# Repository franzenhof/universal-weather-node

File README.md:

# Universal Weather Node — Wireless Sensor Receiver, Weather Station and Gateway for Bresser, Ecowitt / Froggit, TFA and Davis Sensors

**Turn a €20 ESP32 board into the hub of your weather station.** A **Heltec WiFi LoRa 32 V4** (or V3) receives your wireless outdoor station **directly on 868 MHz** — no console, no vendor gateway, no Raspberry Pi, no cloud — measures with its own sensors where you add them, computes dew point, trends and rain totals, and passes everything on to **Home Assistant (MQTT)**, **Loxone**, its own **web dashboard**, **weather networks** and, optionally, **LoRaWAN**.

<!-- help:skip -->

<!-- /help:skip -->

## What to Buy

For a wireless station — no soldering, no custom PCB:

| Part | Notes | Approx. price |
|------|-------|---------------|
| **Heltec WiFi LoRa 32 V4** *(strongly recommended — firmware 4.x)* or **V3 / V3.1 / V3.2** *(legacy)* | The **868 MHz** version (EU). The **V4** has an RF front end with a low-noise amplifier (helps with weak or distant sensors) and 2 MB PSRAM (ESP32-S3R2; used for the history, large buffers and HTTPS since 2.0.0-rc.9) plus 16 MB flash; the firmware detects it and switches the front end itself. **The V4 is strongly recommended:** this 3.x line is legacy (bug fixes only); all new functions come with firmware 4.x, which runs on the V4 only. On a V3, 3.x keeps working. For wired sensors (Davis cups and vane, reed switches, DS18B20 …) use the [custom PCB v2.0](docs/pcb.md#custom-pcb): it takes a **V3 or a V4** (one socket set each, see [Heltec V3 or V4 on the PCB](docs/pcb.md#heltec-v3-or-v4-on-the-pcb)); the older Rev 1.2 / 1.3 boards take the V3 only. Not supported: **V4-R8** (ESP32-S3R8): its 8 MB octal PSRAM takes GPIO33–37, which the board and the PCB need — buy the standard V4 with the **ESP32-S3R2**. | €20–30 |
| **868 MHz antenna** | The small antenna that comes with the board is fine for sensors nearby. For more range, an external 868 MHz antenna with a u.FL/IPEX-to-SMA pigtail (the [enclosure](docs/minimal-build.md) has an SMA bulkhead). **Never power the board without an antenna.** | €0–15 |
| **USB-C power supply** 5 V, ≥ 1 A, with cable | any phone charger | €5–10 |
| **BME280 module** (I²C, 3.3 V) — *recommended* | Adds the air pressure (pressure trend, weather networks); four jumper wires, see [Minimal Wireless Build](docs/minimal-build.md). Must be a BME280, not a BMP280. Not needed if an Ecowitt WS69 pressure module or a WN32P already sends pressure. | €5–10 |
| **Enclosure** — optional | 3D-printable case with a separate ventilated BME280 chamber in [`3dprint/`](3dprint/README.md) (designed for the V3 — check the fit for a V4), or any small box in a dry, sheltered place | – |
| **Your wireless sensors** | 868 MHz versions of Bresser 5/6/7-in-1 and other Bresser sensors, Ecowitt / Froggit, TFA / LaCrosse IT+; Davis Vantage Pro2 / Vue EU (experimental) | – |

Prices are rough guides and vary by shop. For the installation you need a computer with **Chrome or Edge** once.

## Quick Start (wireless station, about 15 minutes)

**You need:** the parts from [What to Buy](#what-to-buy) — a **Heltec WiFi LoRa 32 V4 or V3** (see [installation](docs/installation.md#installing-the-firmware-browser-no-software)) with its **868 MHz antenna**, a USB-C power supply, and a wireless outdoor station — **Bresser** 5/6/7-in-1, **Ecowitt / Froggit** (WS69, WS80, WS85, WS90, WH31, WN34, WH51, WH57, air quality, leak …) or **TFA / LaCrosse IT+**. Recommended: a **BME280** module for the air pressure (four jumper wires, see [Minimal Wireless Build](docs/minimal-build.md)).

1. **Install the firmware in the browser** — Chrome/Edge, [web.esphome.io](https://web.esphome.io), the `-factory.bin` from [`firmware/`](firmware/). Step by step: [Installing the Firmware](docs/installation.md#installing-the-firmware-browser-no-software).
2. **Connect your phone** to the Wi-Fi **`WeatherNode`** and open **http://192.168.4.1** (opens by itself on most phones).
3. **Choose your Wi-Fi** (*Configure WiFi*), save. The node restarts and joins your network.
4. **Open the IP address shown on the display** (in your own network). The **setup wizard** starts by itself and takes you through language, your wireless station (it searches by itself for Bresser, Ecowitt / Froggit and TFA — mark yours with ★, hide the neighbours'), location and altitude, units, an admin password, and optionally [MQTT for Home Assistant](docs/mqtt-home-assistant.md), [weather networks](docs/weather-networks.md) and Loxone. Every step can be skipped — see [Setup Wizard](docs/installation.md#setup-wizard).
5. **Done.** The dashboard shows live values after one measurement cycle; everything can be changed later under **Settings**.

Wired sensors (Davis, reed switches, DS18B20 …) need one of the [custom PCBs](docs/pcb.md#custom-pcb) — see [Hardware](docs/pcb.md#hardware). [LoRaWAN](docs/lorawan.md) is off by default; switch it on for sites without Wi-Fi.

## Features

- 📻 **Up to 32 wireless sensors received directly** — Bresser 5/6/7-in-1 and other Bresser sensors, Ecowitt / Froggit (Fine Offset) outdoor arrays, thermo-hygro, soil, rain, lightning, air quality (PM2.5, CO₂), leak and leaf-wetness sensors, TFA / LaCrosse IT+, and Davis Vantage Pro2 / Vue (experimental); type detected automatically. Every sensor with all its values in the dashboard, REST API and MQTT; per value you choose the source for the main readings (board or wireless, automatic fallback). *(Many Ecowitt / Froggit types and IT+ 17.241 kbit/s confirmed with real sensors; some types only decoded from published frames — see [Wireless Sensors](docs/wireless-sensors.md).)*
- 🌐 **Built-in web dashboard** with live values, warnings, rain totals (hour … year), wind rose and trend charts — works without internet; plus a REST API
- 🏠 **MQTT + Home Assistant** auto-discovery (TLS-capable) — every value, derived value and warning as an entity, plus one HA device per listed wireless sensor; **Loxone** via UDP push or HTTP
- ☁️ **Direct uploads to weather networks** — AWEKAS, Weather Underground, Weathercloud, Wetternetzwerk.pro, Windy, openSenseMap, Met Office WOW, CWOP — plus your own HTTP uploads with placeholders
- 🔔 **Alarms and push notifications** — rules such as gust, frost, leak, lightning or "sensor silent" to ntfy, Pushover, Telegram, MQTT or a webhook
- 🧮 **Computed on the node:** dew point, feels-like, cloud base, VPD, 3-h pressure tendency with a weather trend, temperature trend, rain last hour / 24 h / today / yesterday / week / month / year, sunshine duration, frost / fog / sultry warnings, WMO wind (3-s gusts, 10-min values)
- 🧩 **Everything runs on the ESP32** — no PC, Raspberry Pi, script or cloud service; sensors are read directly, Wi-Fi is output only
- 🔧 **Set up from your phone** — browser installation, config portal, web settings, firmware updates over Wi-Fi; a built-in **radio trace** (diagnostic file) helps us add new sensors; install the dashboard as an **app on the phone's home screen** (offline over HTTPS)
- 📡 **Optional:** LoRaWAN (ChirpStack / TTN) for sites without Wi-Fi, and a custom PCB for Davis and other wired sensors, heater/fan outputs, UV, Victron VE.Direct

<!-- help:skip -->

<!-- /help:skip -->

**Current release:** [3.0.0](firmware/universal-weather-node-3.0.0.bin) ([factory image](firmware/universal-weather-node-3.0.0-factory.bin) for the first installation) — see the [Changelog](CHANGELOG.md#300). Legacy line: bug fixes only; the new functions are in [4.0.0](https://github.com/franzenhof/universal-weather-node) for the Heltec V4. Branches: **`3.x`** = the old line (Heltec V3 and V4; continuation of `2.x`), **`main`** = 4.x (Heltec V4 only), **`2.x`** = ended with 2.0.5, **`1.x`** = the old 1.x line (archive).

## Documentation

| I want to … | Read |
|-------------|------|
| install the firmware, open the config portal, update over Wi-Fi | [Installation and First Setup](docs/installation.md) |
| receive my Bresser / Ecowitt / Froggit / TFA / Davis sensors, record a radio trace | [Wireless Sensors](docs/wireless-sensors.md) |
| build a station without the custom PCB | [Minimal Wireless Build](docs/minimal-build.md) |
| see the dashboard, status page or REST API | [Web Interface](docs/web-dashboard.md) |
| build my own display / app | [HTTP API for Your Own Display](docs/api.md) — contract, examples, mock server |
| connect Home Assistant (MQTT) | [MQTT and Home Assistant](docs/mqtt-home-assistant.md) |
| upload to AWEKAS, Weather Underground, Windy, CWOP … or any HTTP service | [Weather Networks](docs/weather-networks.md) |
| get a push message (ntfy, Pushover, Telegram), MQTT or webhook alarm | [Alarms and Notifications](docs/alarms.md) |
| feed a Loxone Miniserver | [Loxone](docs/loxone.md) |
| use LoRaWAN (ChirpStack / TTN), payload formats, low-power mode | [LoRaWAN](docs/lorawan.md) |
| wire Davis and other sensors with the PCB, order the PCB | [Custom PCB and Wired Sensors](docs/pcb.md) |
| understand measurement, derived values and units | [Measurement, Derived Values and Units](docs/values.md) |
| look up all settings and parameter IDs | [Configuration](docs/settings.md) |
| fix a problem | [Troubleshooting](docs/troubleshooting.md) |
| build from source and run the tests | [Developer Notes](docs/development.md) |
| see what changed between versions | [Changelog](CHANGELOG.md) |

---

## How It Fits Together

The node reads every sensor **directly** — 868 MHz radio decoded by its own LoRa chip, or wired inputs, I²C / 1-Wire on the PCB — processes the values itself and only **sends** them out. It never fetches or receives sensor data over Wi-Fi.

```
 Bresser / Ecowitt / TFA / Davis ~ 868 MHz ~┐               ┌─► Wi-Fi ──► Web dashboard / REST API / phone app in your LAN
   (up to 32 wireless sensors)              │               ├─► Wi-Fi ──► MQTT broker ──► Home Assistant, ...
 BME280 (I²C, recommended) ─────────────────┤               ├─► Wi-Fi ──► AWEKAS, Weather Underground, Windy, WOW, CWOP, ...
 PCB only:                                  ├──► Weather ───┼─► Wi-Fi ──► Alarms: ntfy, Pushover, Telegram, MQTT, webhook
   Davis / generic wind + rain ─────────────┤     Node      ├─► Wi-Fi ──► Loxone (UDP / HTTP), your own HTTP uploads
   DS18B20, UV, AUX, Victron ───────────────┘  (Heltec V4   ├─► OLED display on the board
                                                  or V3)    └─► LoRaWAN (optional) ──► ChirpStack / TTN ──► Grafana, ...
```

The node runs continuously (no deep sleep). It samples the sensors every few seconds and combines the samples into one measurement per **cycle** (default 30 s); each output sends on its own interval (LoRaWAN and MQTT default 300 s). Alarm rules are checked every 30 s and send their message as soon as a rule fires; MQTT can publish faster than the cycle (down to seconds).

## The Project in Pictures

<!-- help:skip -->

<table>
  <tr>
    <td align="center" width="25%">
      
      <br><strong>3D-printed case (Rev 1.2)</strong>
    </td>
    <td align="center" width="25%">
      
      <br><strong>Davis rain &amp; wind sensor</strong>
    </td>
    <td align="center" width="50%">
      
      <br><strong>Built-in web dashboard</strong>
    </td>
  </tr>
  <tr>
    <td align="center">
      
      <br><strong>Enclosure for the minimal build</strong>
    </td>
    <td align="center">
      
      <br><strong>Dashboard on the phone (installable as an app)</strong>
    </td>
    <td align="center">
      
      <br><strong>Grafana: wind data via LoRaWAN</strong>
    </td>
  </tr>
</table>
<!-- /help:skip -->

*(Pictures are only shown on the project page, not in the device's built-in help.)*

---

## License

This project is fully open source and dual-licensed:

* **Software / firmware:** [MIT License](LICENSE-SOFTWARE) — use, modify and distribute freely.
* **Hardware (schematics, PCB, 3D files):** [CERN-OHL-P v2](LICENSE-HARDWARE) (permissive) — manufacture, modify and distribute freely.

*Developed with 🚜 and 💻 by Gerhard Massenbichler at Franzenhof.*

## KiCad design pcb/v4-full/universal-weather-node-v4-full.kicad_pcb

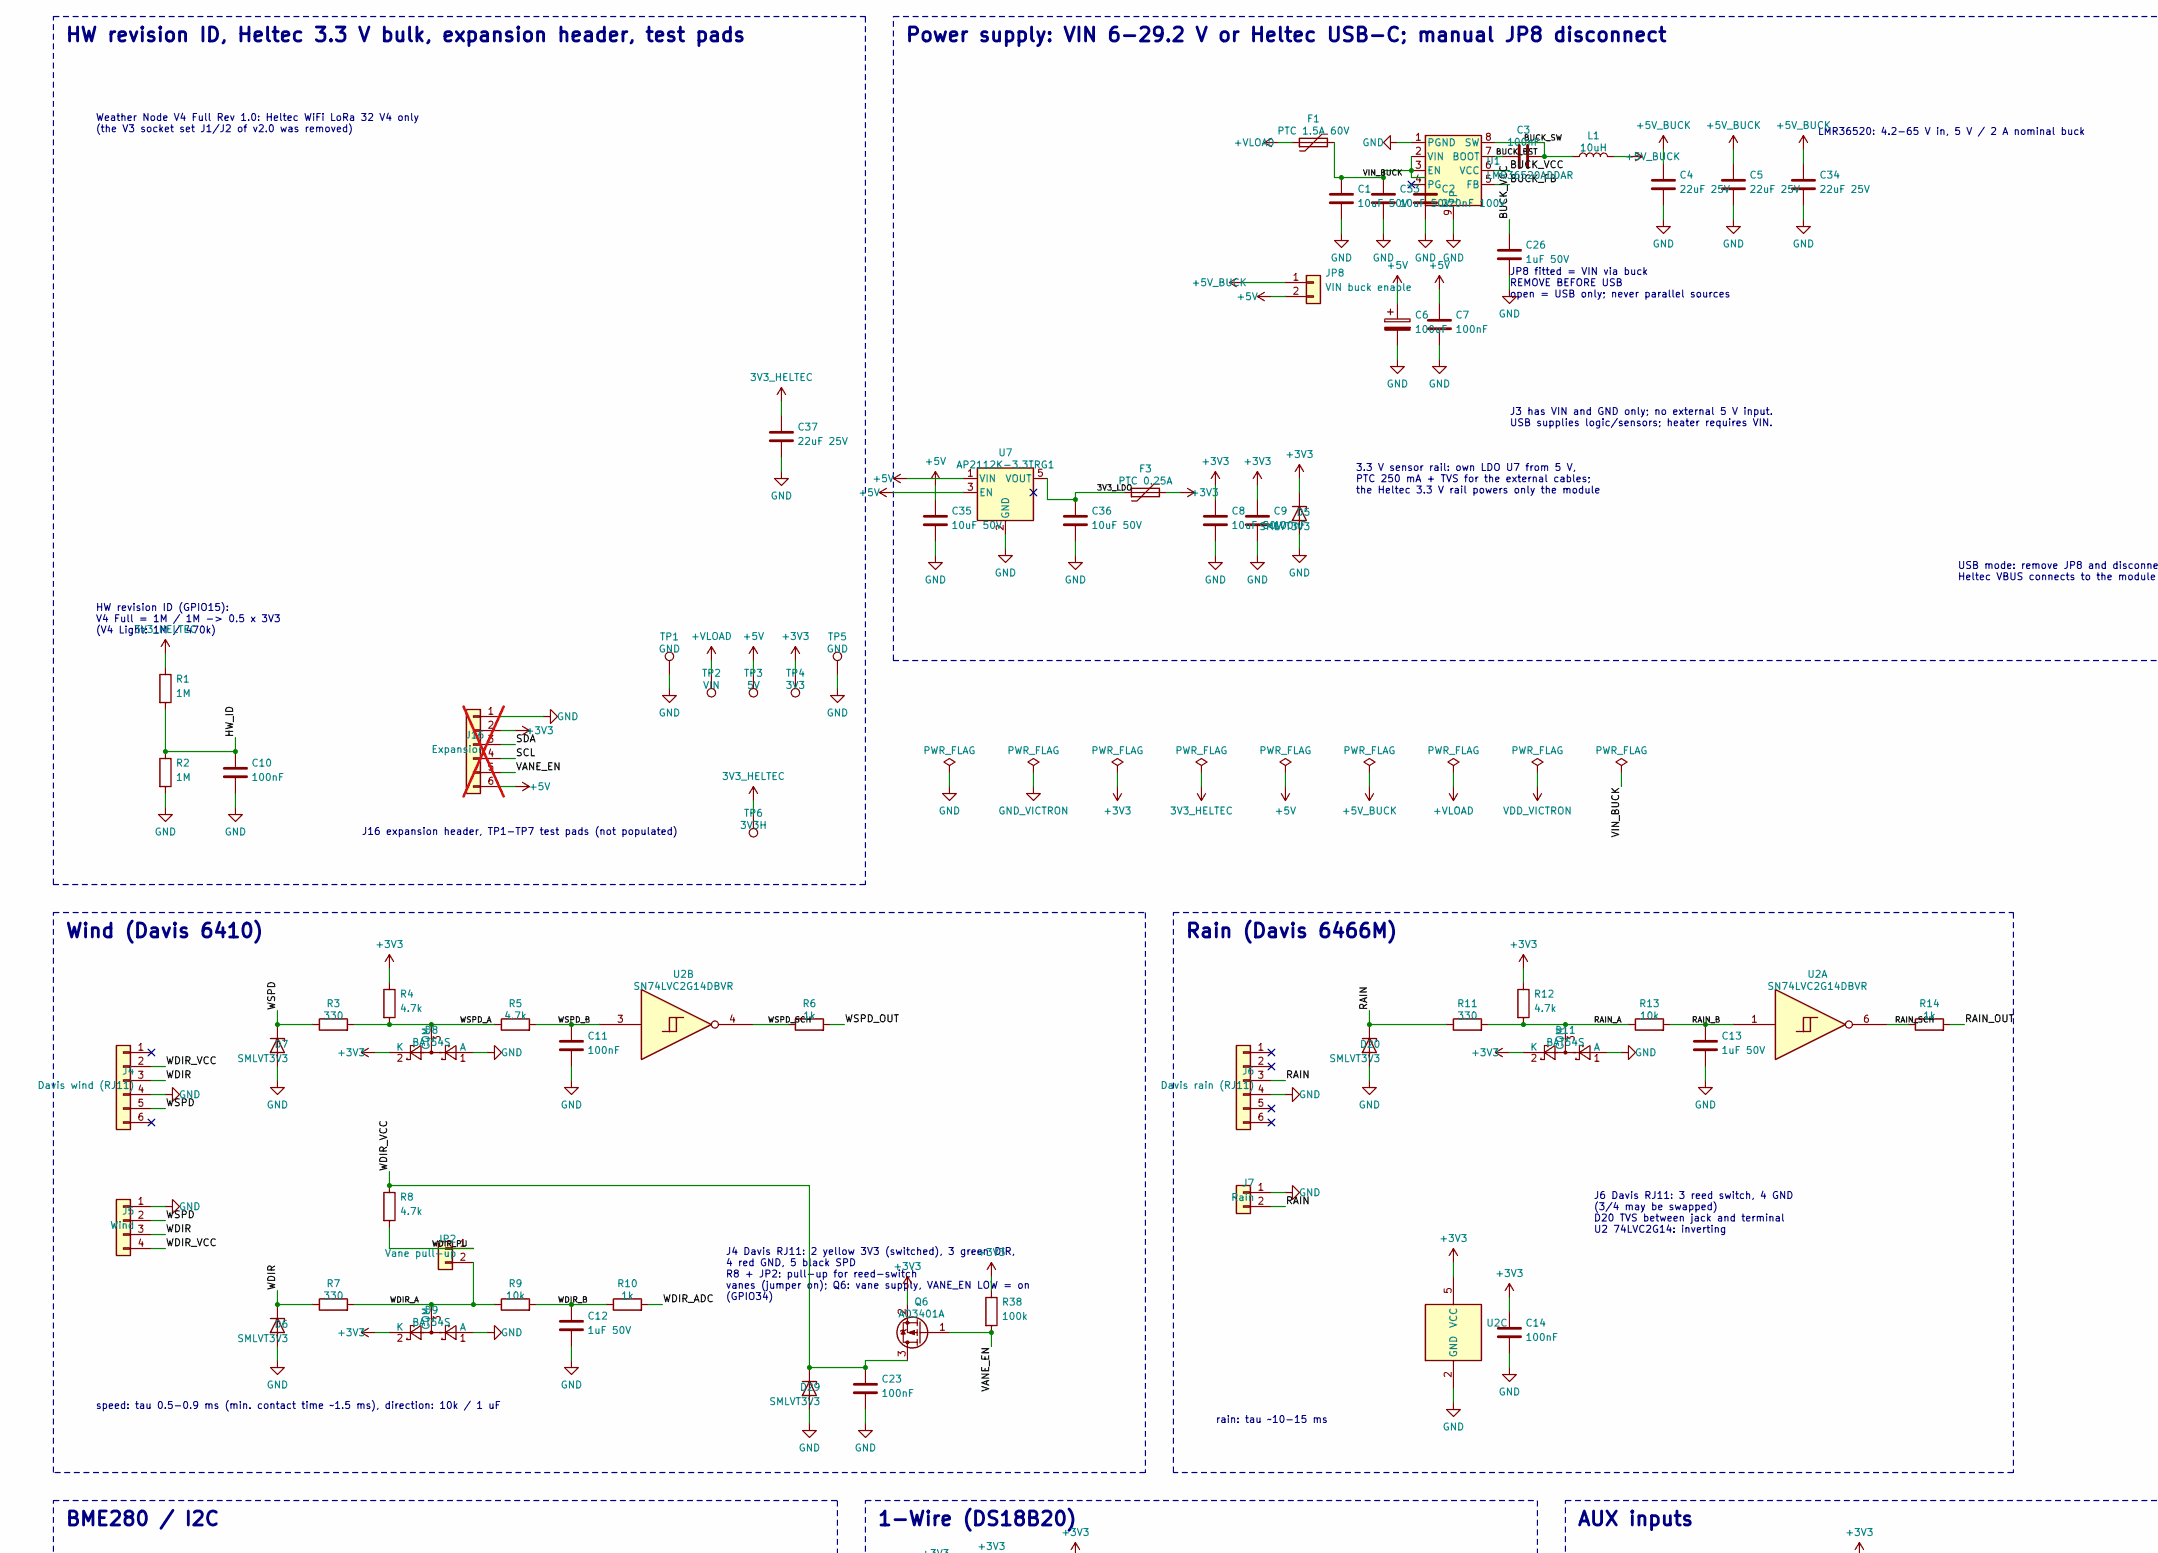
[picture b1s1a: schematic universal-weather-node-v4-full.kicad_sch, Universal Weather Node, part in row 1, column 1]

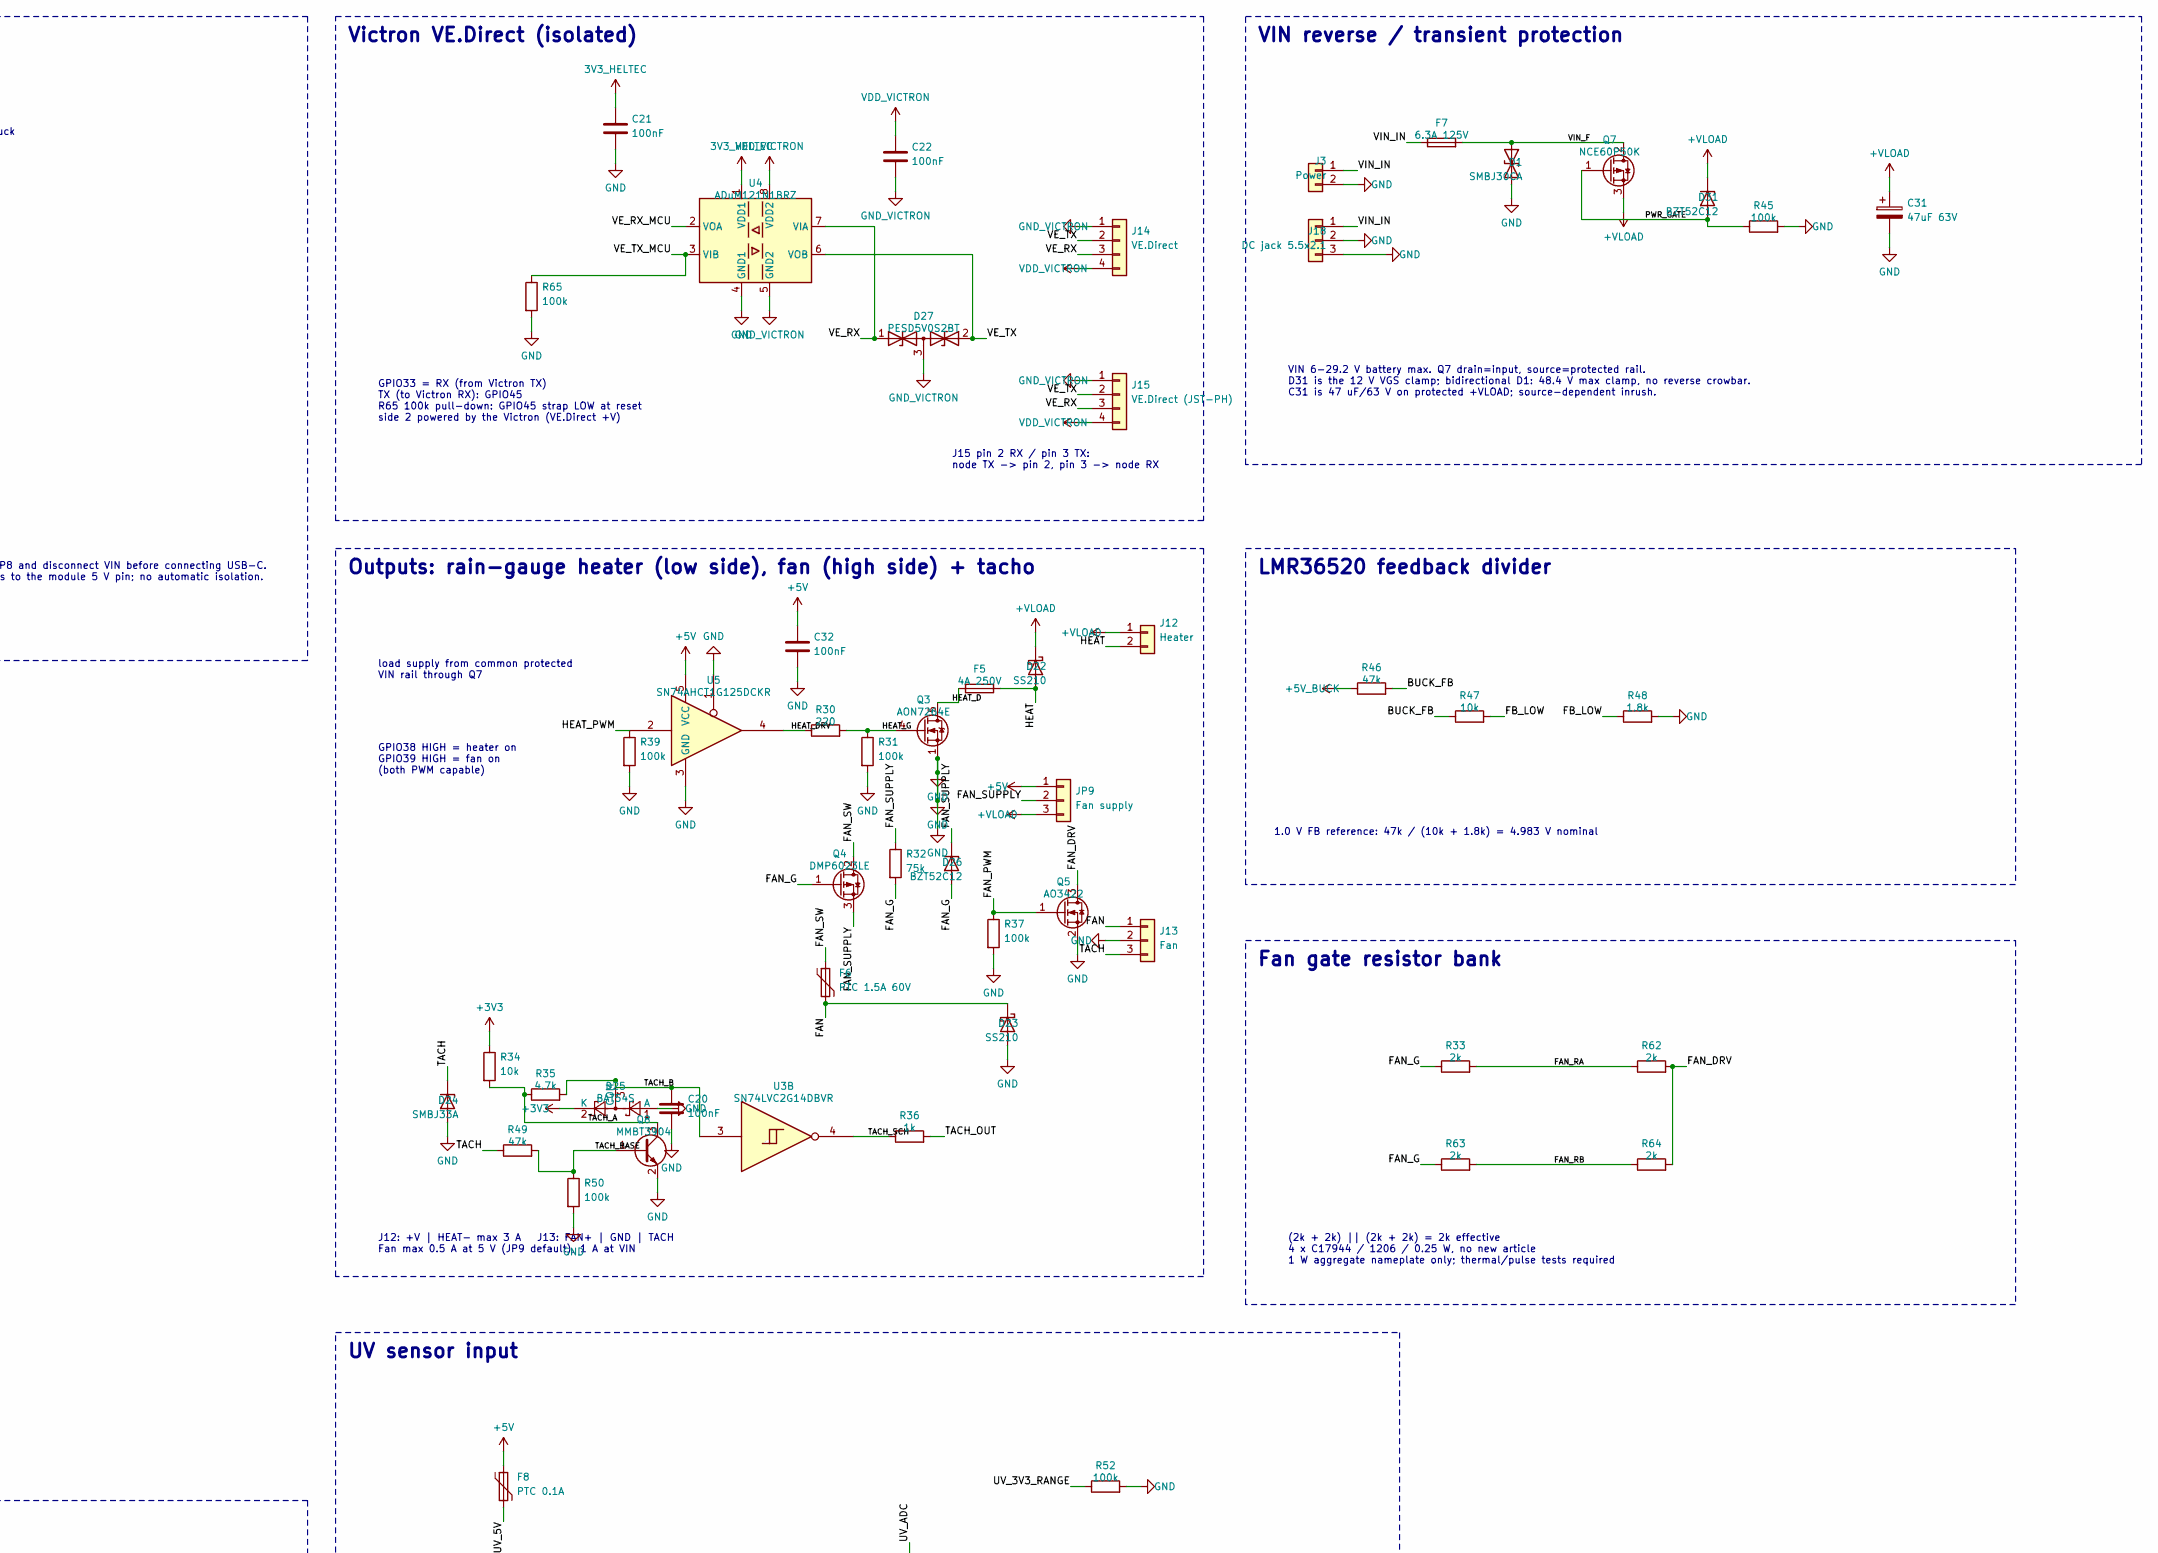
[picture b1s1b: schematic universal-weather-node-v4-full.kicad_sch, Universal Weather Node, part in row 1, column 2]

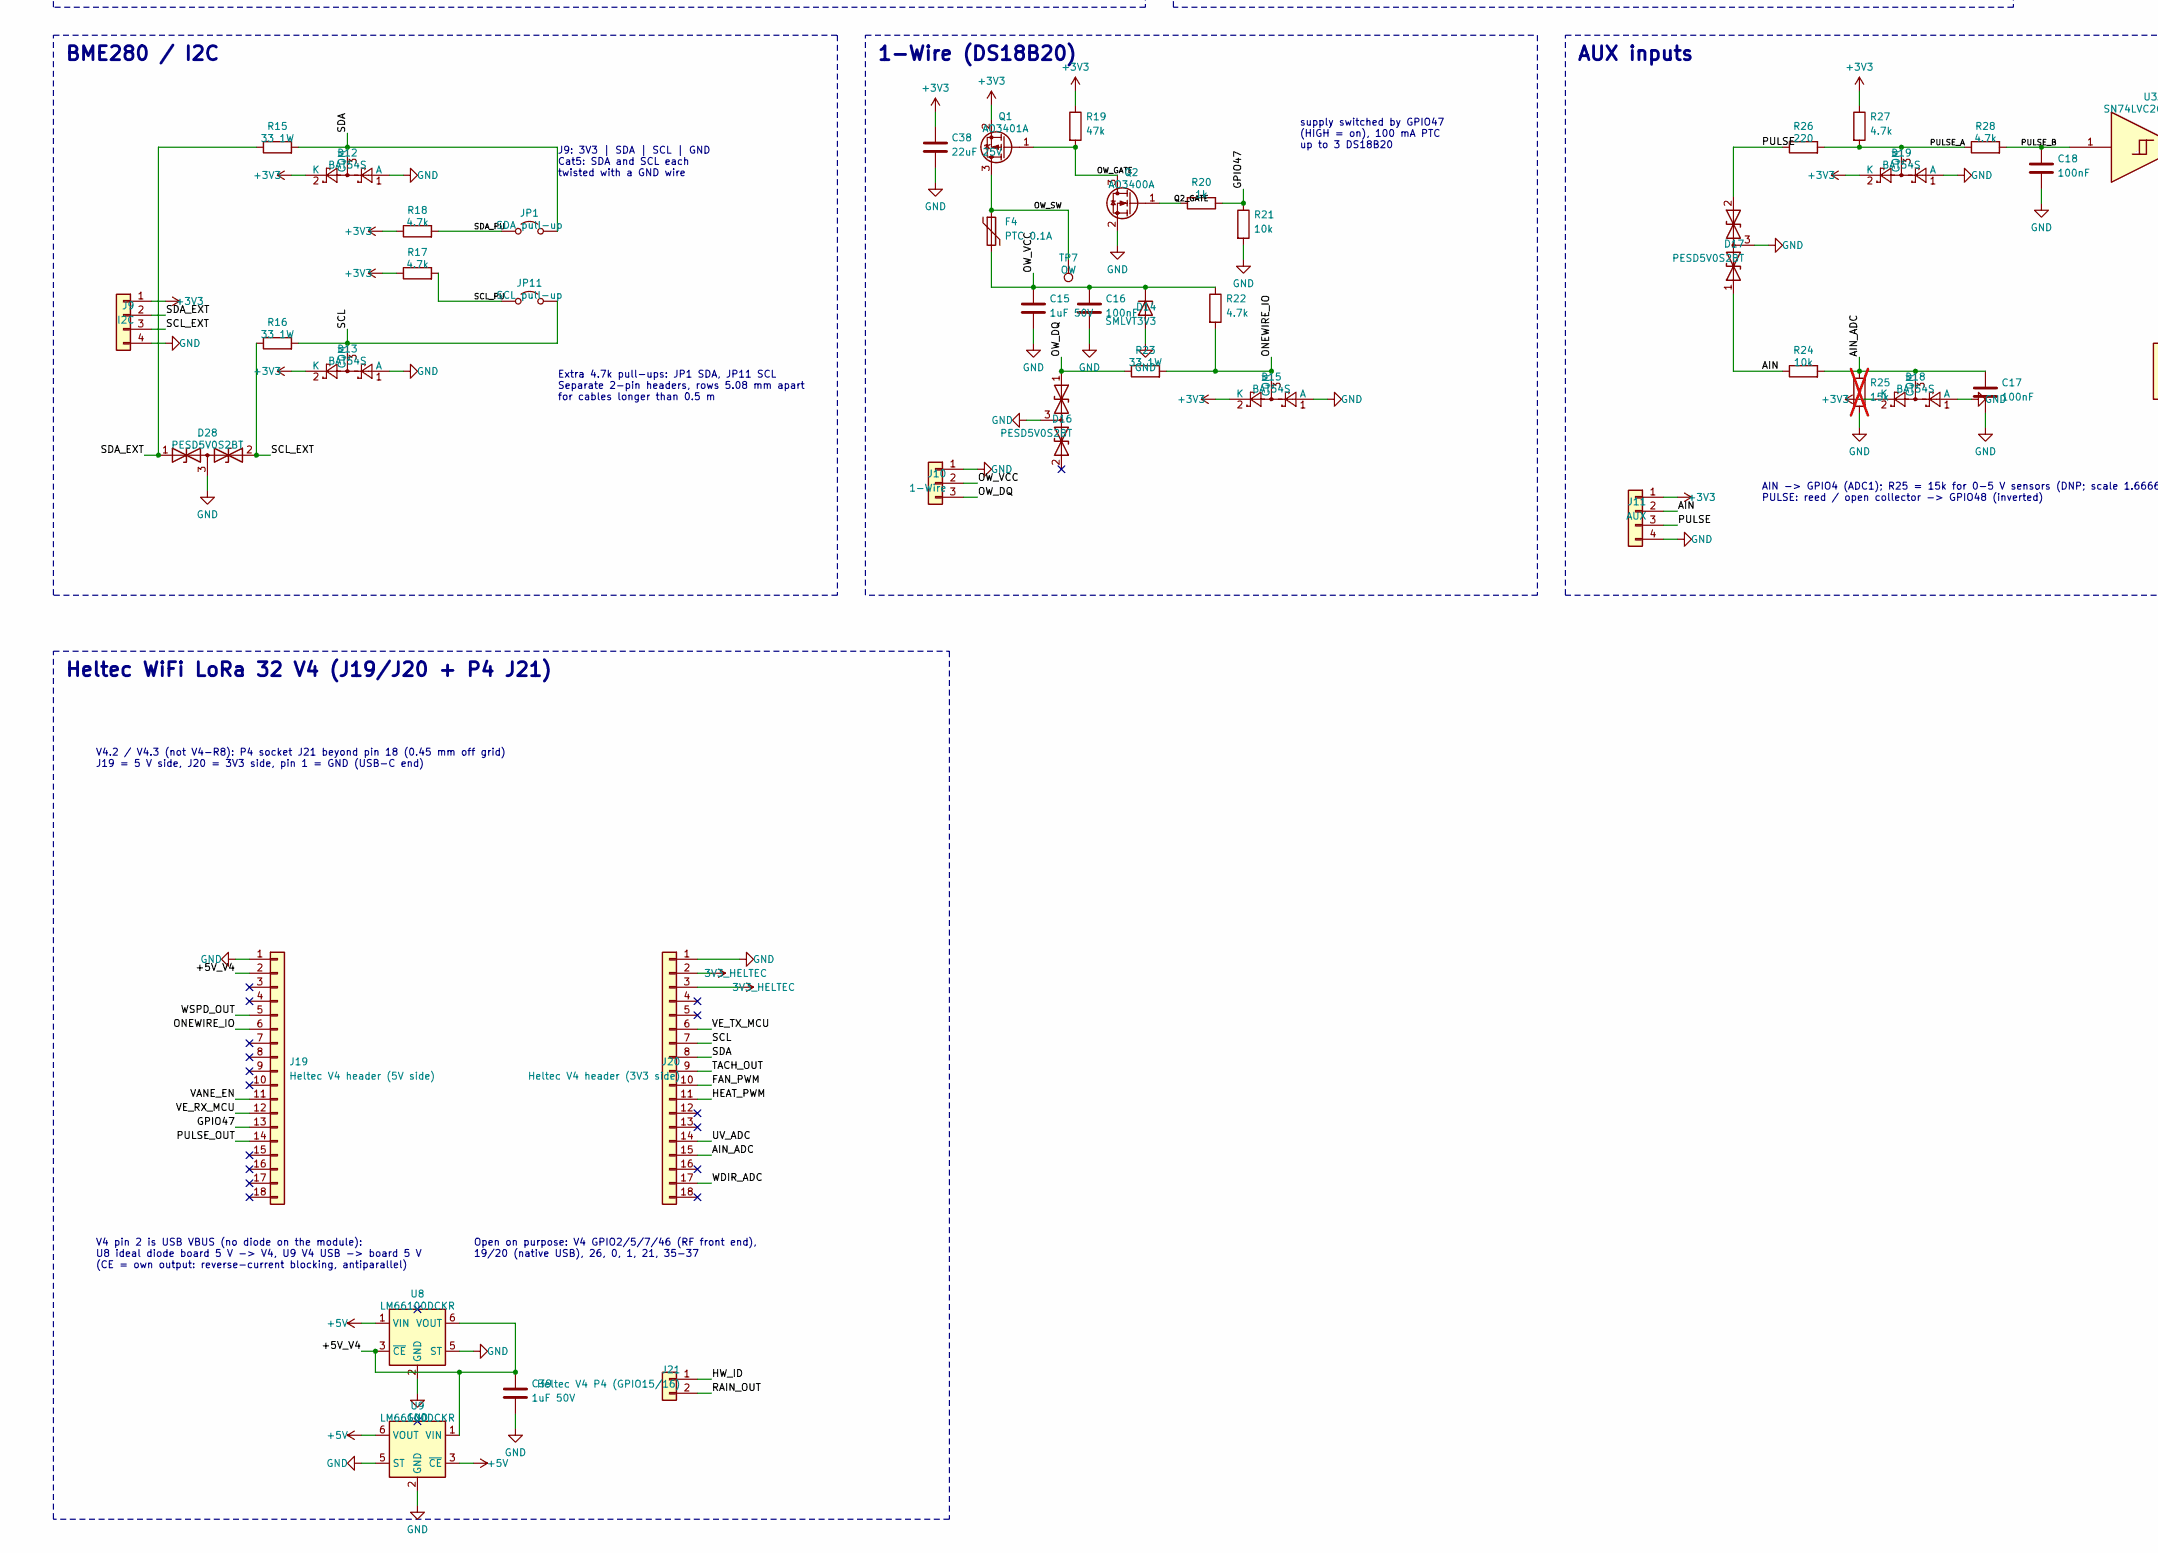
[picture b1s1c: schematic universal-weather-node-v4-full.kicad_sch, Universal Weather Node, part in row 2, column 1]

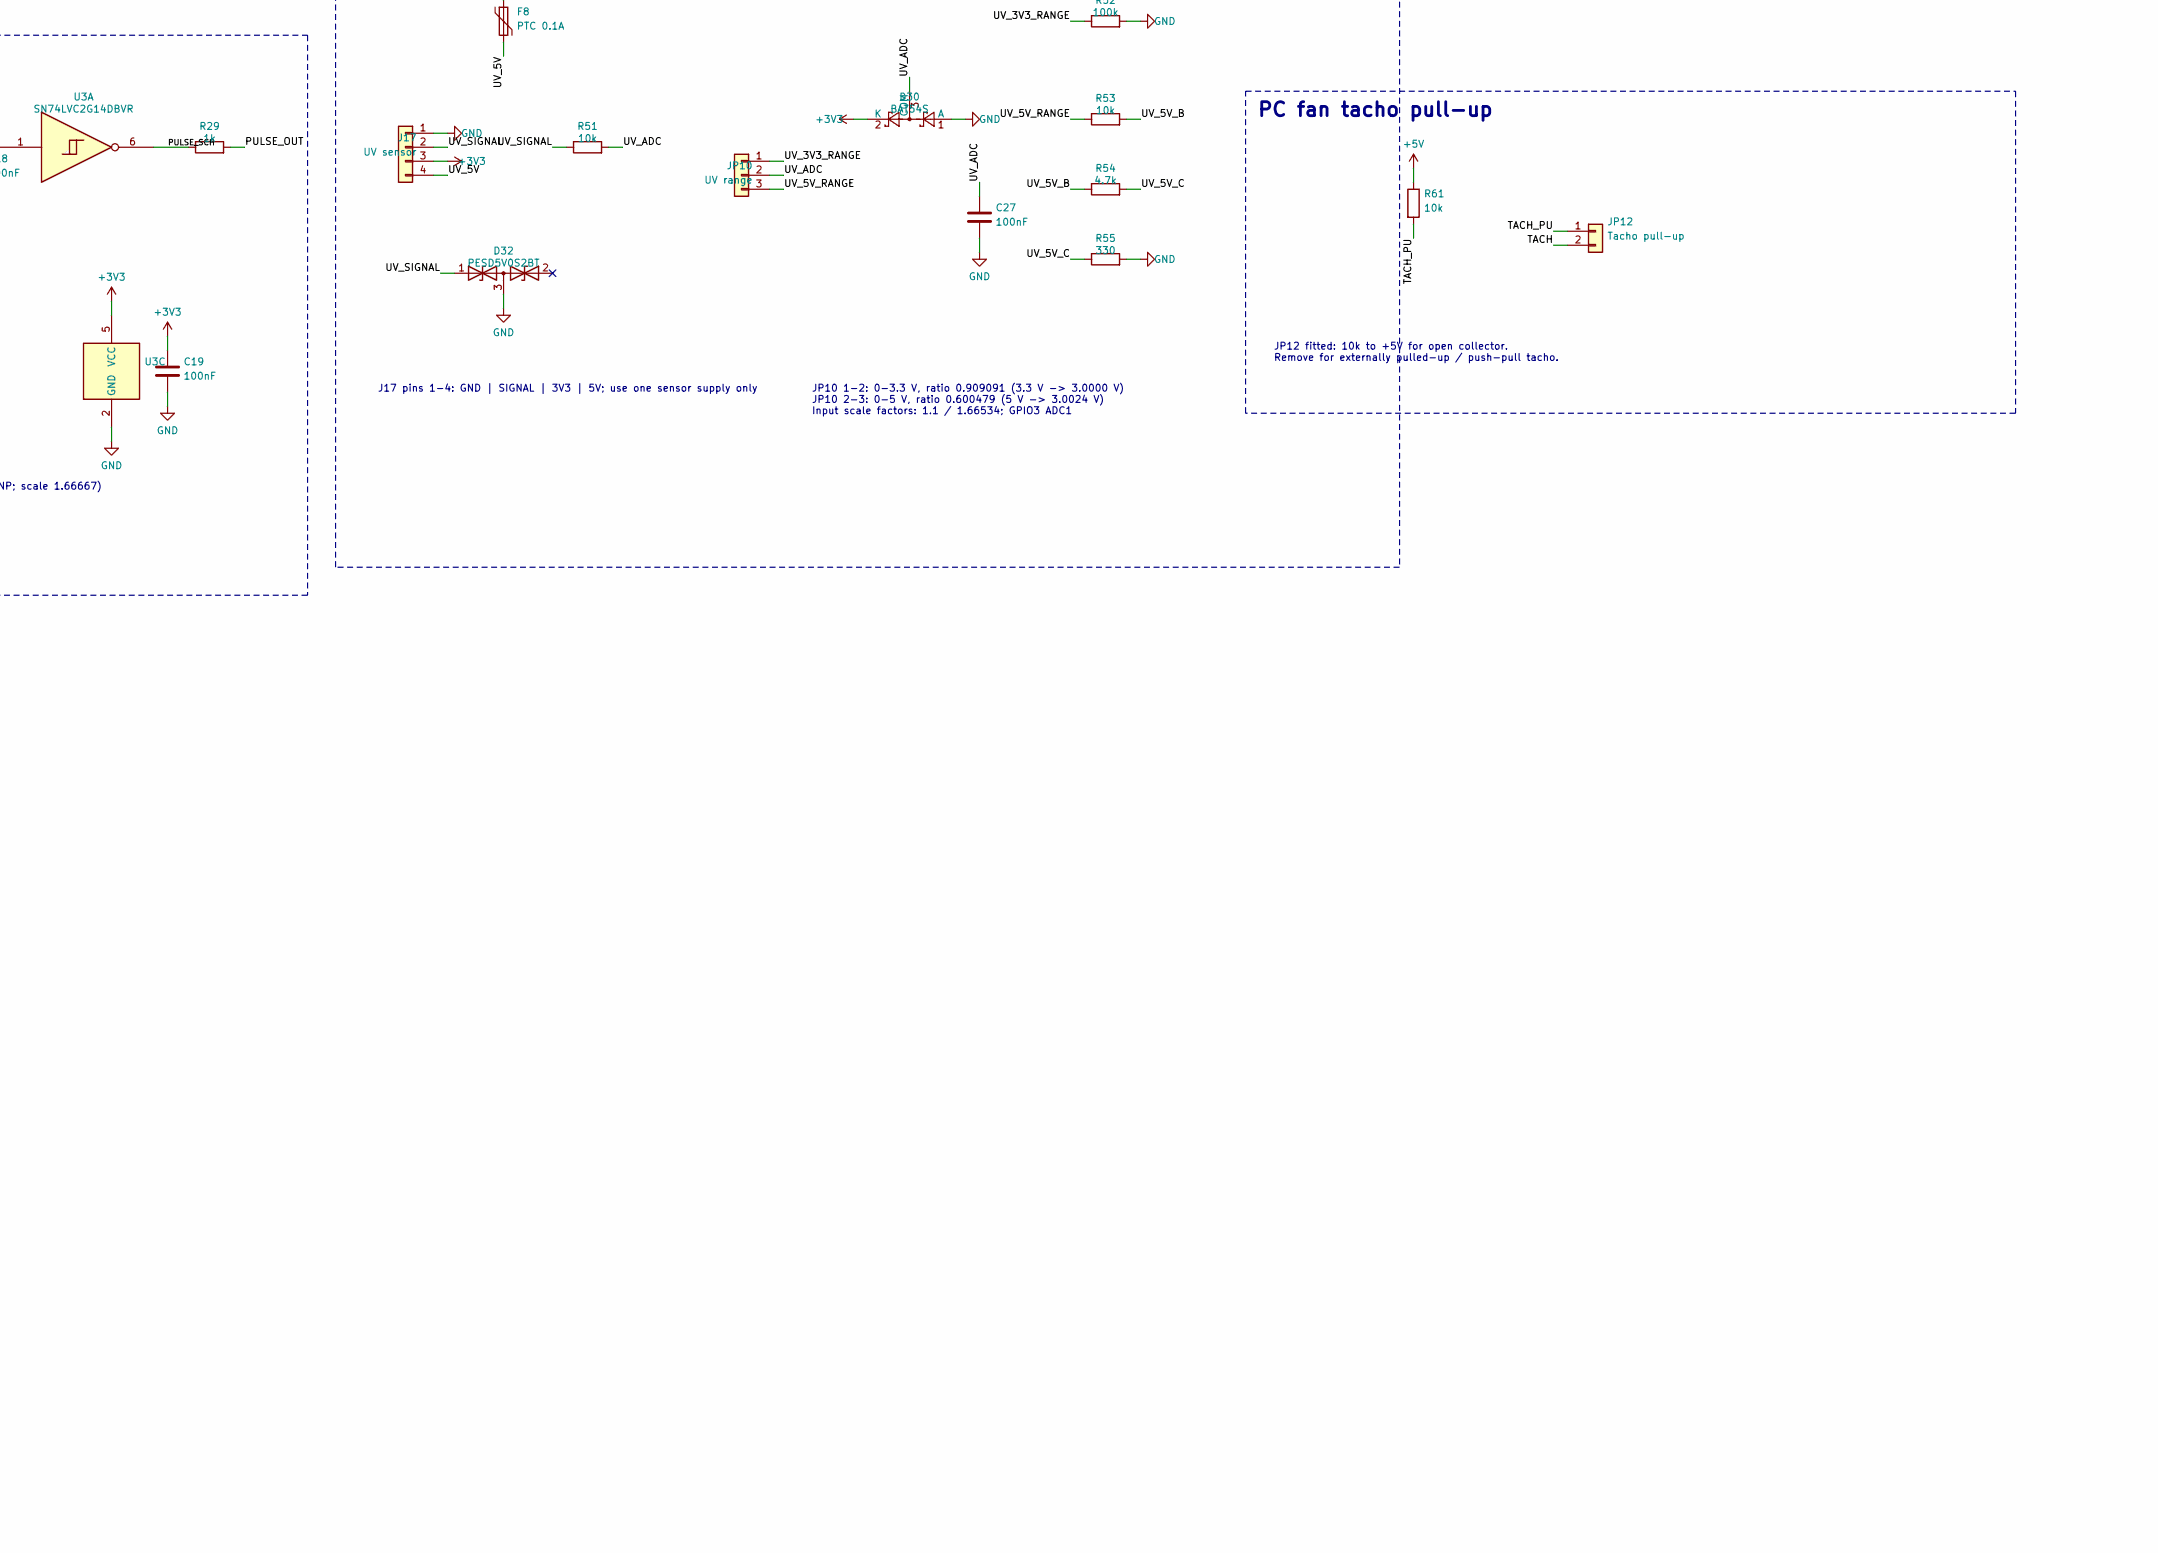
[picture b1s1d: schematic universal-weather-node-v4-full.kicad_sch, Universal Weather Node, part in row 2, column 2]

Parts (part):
C1, C8, C33, C35, C36: 10uF 50V; C_1210_3225Metric; MPN Murata GRM32ER71H106KA12L (10 uF, 50 V,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; LCSC C77102
C2: 220nF 100V; C_0805_2012Metric; MPN Yageo CC0805KKX7R0BB224; LCSC C513710
C3, C7, C9, C10, C11, C14, C16, C17, C18, C19, C20, C21, C22, C23, C27: 100nF; C_0805_2012Metric; MPN Yageo CC0805KRX7R9BB104; LCSC C49678
C4, C5, C38: 22uF 25V; C_0805_2012Metric; MPN Samsung CL21A226MAQNNNE (22 uF, 25 V, X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; LCSC C45783
C6: 100uF; CP_Elec_6.3x7.7; MPN DMBJ RVT1E101M0607 (25V); LCSC C970685
C12, C13, C15, C26, C39: 1uF 50V; C_0805_2012Metric; MPN Samsung CL21B105KBFNNNE (1 uF 50 V X7R); LCSC C28323
C31: 47uF 63V; CP_Elec_8x10; MPN Nichicon UCD1J470MNL1GS (47 uF, 63 V, S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; LCSC C445452
C32: 100nF; C_0402_1005Metric; MPN Samsung CL05B104KO5NNNC (100 nF, 16 V, 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; LCSC C1525
C34, C37: 22uF 25V; C_1210_3225Metric; MPN Murata GRM32ER71E226KE15L (22 uF, 25 V,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; LCSC C21397
D1: SMBJ30CA; D_SMB; MPN Littelfuse SMBJ30CA; LCSC C83847
D5, D6, D7, D14, D20, D29: SMLVT3V3; D_SMB; MPN SMLVT3V3; LCSC C283619
D8, D9, D11, D12, D13, D15, D18, D19, D25, D30: BAT54S; SOT-23; MPN R+O BAT54S (series pair, SOT-23; prefer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; LCSC C7420333
D16, D17, D27, D28, D32: PESD5V0S2BT; SOT-23; MPN Nexperia PESD5V0S2BT,215; LCSC C49338
D22, D23: SS210; D_SMA; MPN SS210 (2 A, 100 V Schottky, SMA; basic); LCSC C14996
D24: SMBJ33A; D_SMB; MPN SMBJ33A (33 V standoff, unidirectional,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; LCSC C19077586
D26, D31: BZT52C12; D_SOD-123; MPN BZT52C12 (12 V zener, SOD-123; preferre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; LCSC C19077410
F1, F6: PTC 1.5A 60V; Fuse_2920_7451Metric; MPN LUTE 2920L150/60GR (1.5 A hold, 60 V); LCSC C19078738
F3: PTC 0.25A; Fuse_1206_3216Metric; MPN nSMD025 (16V); LCSC C70068
F4, F8: PTC 0.1A; Fuse_1206_3216Metric; MPN nSMD010 (60V); LCSC C70065
F5: 4A 250V; Fuse_Littelfuse-NANO2-451_453; MPN SETsafe SCT6125T4A250V (4 A, 250 V); LCSC C19712551
F7: 6.3A 125V; Fuse_Littelfuse-NANO2-451_453; MPN Littelfuse 045106.3MRL (6.3 A, 125 VDC); LCSC C178982
J3: Power; TerminalBlock_Phoenix_PT-1,5-2-3.5-H_1x02_P3.50mm_Horizontal; MPN DB125-3.5-2P-GN-S; LCSC C466970
J4: Davis wind (RJ11); RJ12_Amphenol_54601-x06_Horizontal; MPN EVERCOM 5301-6P6C (RJ11/RJ12 6P6C, unsh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; LCSC C3097716
J5: Wind; TerminalBlock_Phoenix_PT-1,5-4-3.5-H_1x04_P3.50mm_Horizontal; MPN DB125-3.5-4P-GN-S; LCSC C2757925
J6: Davis rain (RJ11); RJ12_Amphenol_54601-x06_Horizontal; MPN EVERCOM 5301-6P6C (RJ11/RJ12 6P6C, unsh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; LCSC C3097716
J7: Rain; TerminalBlock_Phoenix_PT-1,5-2-3.5-H_1x02_P3.50mm_Horizontal; MPN DB125-3.5-2P-GN-S; LCSC C466970
J9: I2C; TerminalBlock_Phoenix_PT-1,5-4-3.5-H_1x04_P3.50mm_Horizontal; MPN DB125-3.5-4P-GN-S; LCSC C2757925
J10: 1-Wire; TerminalBlock_Phoenix_PT-1,5-3-3.5-H_1x03_P3.50mm_Horizontal; MPN DB125-3.5-3P-GN-S; LCSC C466971
J11: AUX; TerminalBlock_Phoenix_PT-1,5-4-3.5-H_1x04_P3.50mm_Horizontal; MPN DB125-3.5-4P-GN-S; LCSC C2757925
J12: Heater; TerminalBlock_Phoenix_PT-1,5-2-3.5-H_1x02_P3.50mm_Horizontal; MPN DB125-3.5-2P-GN-S; LCSC C466970
J13: Fan; TerminalBlock_Phoenix_PT-1,5-3-3.5-H_1x03_P3.50mm_Horizontal; MPN DB125-3.5-3P-GN-S; LCSC C466971
J14: VE.Direct; TerminalBlock_Phoenix_PT-1,5-4-3.5-H_1x04_P3.50mm_Horizontal; MPN DB125-3.5-4P-GN-S; LCSC C2757925
J15: VE.Direct (JST-PH); JST_PH_B4B-PH-K_1x04_P2.00mm_Vertical; MPN JST B4B-PH-K-S(LF)(SN); LCSC C131334
J16: Expansion; PinHeader_1x06_P2.54mm_Vertical; MPN HX PZ2.54-1x6P ZZ; LCSC C32713272; not fitted
J17: UV sensor; TerminalBlock_Phoenix_PT-1,5-4-3.5-H_1x04_P3.50mm_Horizontal; MPN DB125-3.5-4P-GN-S; LCSC C2757925
J18: DC jack 5.5x2.1; BarrelJack_Horizontal; MPN XKB DC-005-5A-2.0 (5.5x2.1 mm, 5 A, 24 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; LCSC C381116
J19: Heltec V4 header (5V side); PinSocket_1x18_P2.54mm_Vertical; MPN Kinghelm KH-2.54FH-1X18P-H8.5; LCSC C2905422
J20: Heltec V4 header (3V3 side); PinSocket_1x18_P2.54mm_Vertical; MPN Kinghelm KH-2.54FH-1X18P-H8.5; LCSC C2905422
J21: Heltec V4 P4 (GPIO15/16); PinSocket_1x02_P2.54mm_Vertical; MPN SHOU HAN PM2.54-1x2PZZ-H8.5 (1x2 female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; LCSC C54876674
JP1: SDA pull-up; PinHeader_1x02_P2.54mm_Vertical; MPN LXWCONN 254PZ-1x2P-V; LCSC C53055672
JP2: Vane pull-up; PinHeader_1x02_P2.54mm_Vertical; MPN LXWCONN 254PZ-1x2P-V; LCSC C53055672
JP8: VIN buck enable; PinHeader_1x02_P2.54mm_Vertical; MPN LXWCONN 254PZ-1x2P-V; LCSC C53055672
JP9: Fan supply; PinHeader_1x03_P2.54mm_Vertical; MPN BOOMELE 2.54-1*3P; LCSC C49257
JP10: UV range; PinHeader_1x03_P2.54mm_Vertical; MPN BOOMELE 2.54-1*3P; LCSC C49257
JP11: SCL pull-up; PinHeader_1x02_P2.54mm_Vertical; MPN LXWCONN 254PZ-1x2P-V; LCSC C53055672
JP12: Tacho pull-up; PinHeader_1x02_P2.54mm_Vertical; MPN LXWCONN 254PZ-1x2P-V; LCSC C53055672
L1: 10uH; L_Bourns_SRP5030T; MPN Bourns SRP5030T-100M; LCSC C189932
Q1, Q6: AO3401A; SOT-23; MPN AO3401A; LCSC C15127
Q2: AO3400A; SOT-23; MPN AOS AO3400A; LCSC C20917
Q3: AON7264E; Vishay_PowerPAK_1212-8_Single; MPN AOS AON7264E (60 V N-MOSFET, DFN 3.3x3.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; LCSC C431191
Q4: DMP6023LE; SOT-223-3_TabPin2; MPN Diodes Incorporated DMP6023LE-13; LCSC C154901
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
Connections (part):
3V3_HELTEC: C21.1, C37.1, J20.2, J20.3, R1.1, TP6.1, U4.1 (VDD1)
+3V3: C8.1, C9.1, C14.1, C19.1, C38.1, D5.1 (K), D8.2 (K), D9.2 (K), D11.2 (K), D12.2 (K), D13.2 (K), D15.2 (K), D18.2 (K), D19.2 (K), D25.2 (K), D30.2 (K), F3.2, J9.1, J11.1, J16.2, J17.3, Q1.2 (S), Q6.2 (S), R4.1, R12.1, R17.1, R18.1, R19.1, R27.1, R34.1, R38.1, TP4.1, U2.5 (VCC), U3.5 (VCC)
+5V: C6.1, C7.1, C32.1, C35.1, F8.1, J16.6, JP8.2, JP9.1, R61.1, TP3.1, U5.5 (VCC), U7.1 (VIN), U7.3 (EN), U8.1 (VIN), U9.3 (~CE), U9.6 (VOUT)
+5V_BUCK: C4.1, C5.1, C34.1, JP8.1, L1.2, R46.1
+VLOAD: C31.1, D22.1 (K), D31.1 (K), F1.1, J12.1, JP9.3, Q7.3 (S), TP2.1
/3V3_LDO: C36.1, F3.1, U7.5 (VOUT)
/+5V_V4: C39.1, J19.2, U8.3 (~CE), U8.6 (VOUT), U9.1 (VIN)
/AIN: D17.1 (A1), J11.2, R24.1
/AIN_ADC: C17.1, D18.3 (COM), J20.15, R24.2, R25.1
/BUCK_BST: C3.1, U1.7 (BOOT)
/BUCK_FB: R46.2, R47.1, U1.5 (FB)
/BUCK_SW: C3.2, L1.1, U1.8 (SW)
/BUCK_VCC: C26.1, U1.6 (VCC)
/FAN: D23.1 (K), F6.2, J13.1
/FAN_DRV: Q5.3 (D), R62.2, R64.2
/FAN_G: D26.2 (A), Q4.1 (G), R32.2, R33.1, R63.1
/FAN_PWM: J20.10, Q5.1 (G), R37.1
/FAN_RA: R33.2, R62.1
/FAN_RB: R63.2, R64.1
/FAN_SUPPLY: D26.1 (K), JP9.2, Q4.3 (S), R32.1
/FAN_SW: F6.1, Q4.2 (D)
/FB_LOW: R47.2, R48.1
/GPIO47: J19.13, R20.1, R21.1
/HEAT: D22.2 (A), F5.1, J12.2
/HEAT_D: F5.2, Q3.5 (D)
/HEAT_DRV: R30.1, U5.4
/HEAT_G: Q3.4 (G), R30.2, R31.1
/HEAT_PWM: J20.11, R39.1, U5.2
/HW_ID: C10.1, J21.1, R1.2, R2.1
/ONEWIRE_IO: D15.3 (COM), J19.6, R22.2, R23.2
/OW_DQ: D16.1 (A1), J10.3, R23.1
/OW_GATE: Q1.1 (G), Q2.3 (D), R19.2
/OW_SW: F4.1, Q1.3 (D), TP7.1
/OW_VCC: C15.1, C16.1, D14.1 (K), F4.2, J10.2, R22.1
/PULSE: D17.2 (A2), J11.3, R26.1
/PULSE_A: D19.3 (COM), R26.2, R27.2, R28.1
/PULSE_B: C18.1, R28.2, U3.1
/PULSE_OUT: J19.14, R29.2
/PULSE_SCH: R29.1, U3.6
/PWR_GATE: D31.2 (A), Q7.1 (G), R45.1
/Q2_GATE: Q2.1 (G), R20.2
/RAIN: D20.1 (K), J6.3, J7.2, R11.1
/RAIN_A: D11.3 (COM), R11.2, R12.2, R13.1
/RAIN_B: C13.1, R13.2, U2.1
/RAIN_OUT: J21.2, R14.2
/RAIN_SCH: R14.1, U2.6
/SCL: D13.3 (COM), J16.4, J20.7, JP11.2 (B), R16.2
/SCL_EXT: D28.2 (A2), J9.3, R16.1
/SCL_PU: JP11.1 (A), R17.2
/SDA: D12.3 (COM), J16.3, J20.8, JP1.2 (B), R15.2
/SDA_EXT: D28.1 (A1), J9.2, R15.1
/SDA_PU: JP1.1 (A), R18.2
/TACH: D24.1 (K), J13.3, JP12.2, R49.1
/TACH_A: Q8.3 (C), R34.2, R35.1
/TACH_B: C20.1, D25.3 (COM), R35.2, U3.3
/TACH_BASE: Q8.1 (B), R49.2, R50.1
/TACH_OUT: J20.9, R36.2
/TACH_PU: JP12.1, R61.2
/TACH_SCH: R36.1, U3.4
/UV_3V3_RANGE: JP10.1, R52.1
/UV_5V: F8.2, J17.4
/UV_5V_B: R53.2, R54.1
/UV_5V_C: R54.2, R55.1
/UV_5V_RANGE: JP10.3, R53.1
/UV_ADC: C27.1, D30.3 (COM), J20.14, JP10.2, R51.2
/UV_SIGNAL: D32.1 (A1), J17.2, R51.1
/VANE_EN: J16.5, J19.11, Q6.1 (G), R38.2
/VE_RX: D27.1 (A1), J14.3, J15.3, U4.7 (VIA)
/VE_RX_MCU: J19.12, U4.2 (VOA)
/VE_TX: D27.2 (A2), J14.2, J15.2, U4.6 (VOB)
/VE_TX_MCU: J20.6, R65.1, U4.3 (VIB)
/VIN_BUCK: C1.1, C2.1, C33.1, F1.2, U1.2 (VIN), U1.3 (EN)
/VIN_F: D1.1 (A1), F7.2, Q7.2 (D)
/VIN_IN: F7.1, J3.1, J18.1
/WDIR: D6.1 (K), J4.3, J5.3, R7.1
/WDIR_A: D9.3 (COM), JP2.2, R7.2, R9.1
/WDIR_ADC: J20.17, R10.2
/WDIR_B: C12.1, R9.2, R10.1
/WDIR_PU: JP2.1, R8.2
/WDIR_VCC: C23.1, D29.1 (K), J4.2, J5.4, Q6.3 (D), R8.1
/WSPD: D7.1 (K), J4.5, J5.2, R3.1
/WSPD_A: D8.3 (COM), R3.2, R4.2, R5.1
/WSPD_B: C11.1, R5.2, U2.3
/WSPD_OUT: J19.5, R6.2
/WSPD_SCH: R6.1, U2.4
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
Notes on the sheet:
HW revision ID, Heltec 3.3 V bulk, expansion header, test pads
Weather Node V4 Full Rev 1.0: Heltec WiFi LoRa 32 V4 only (the V3 socket set J1/J2 of v2.0 was removed)
HW revision ID (GPIO15): V4 Full = 1M / 1M -> 0.5 x 3V3 (V4 Light: 1M / 470k)
J16 expansion header, TP1-TP7 test pads (not populated)
Heltec WiFi LoRa 32 V4 (J19/J20 + P4 J21)
V4.2 / V4.3 (not V4-R8): P4 socket J21 beyond pin 18 (0.45 mm off grid) J19 = 5 V side, J20 = 3V3 side, pin 1 = GND (USB-C end)
V4 pin 2 is USB VBUS (no diode on the module): U8 ideal diode board 5 V -> V4, U9 V4 USB -> board 5 V (CE = own output: reverse-current blocking, antiparallel)
Open on purpose: V4 GPIO2/5/7/46 (RF front end), 19/20 (native USB), 26, 0, 1, 21, 35-37
Power supply: VIN 6-29.2 V or Heltec USB-C; manual JP8 disconnect
LMR36520: 4.2-65 V in, 5 V / 2 A nominal buck
J3 has VIN and GND only; no external 5 V input. USB supplies logic/sensors; heater requires VIN.
JP8 fitted = VIN via buck REMOVE BEFORE USB open = USB only; never parallel sources
USB mode: remove JP8 and disconnect VIN before connecting USB-C. Heltec VBUS connects to the module 5 V pin; no automatic isolation.
3.3 V sensor rail: own LDO U7 from 5 V, PTC 250 mA + TVS for the external cables; the Heltec 3.3 V rail powers only the module
VIN reverse / transient protection
VIN 6-29.2 V battery max. Q7 drain=input, source=protected rail. D31 is the 12 V VGS clamp; bidirectional D1: 48.4 V max clamp, no reverse crowbar. C31 is 47 uF/63 V on protected +VLOAD; source-dependent inrush.
LMR36520 feedback divider
1.0 V FB reference: 47k / (10k + 1.8k) = 4.983 V nominal
PC fan tacho pull-up
JP12 fitted: 10k to +5V for open collector. Remove for externally pulled-up / push-pull tacho.
Fan gate resistor bank
(2k + 2k) || (2k + 2k) = 2k effective 4 x C17944 / 1206 / 0.25 W, no new article 1 W aggregate nameplate only; thermal/pulse tests required
Victron VE.Direct (isolated)
GPIO33 = RX (from Victron TX) TX (to Victron RX): GPIO45 R65 100k pull-down: GPIO45 strap LOW at reset side 2 powered by the Victron (VE.Direct +V)
J15 pin 2 RX / pin 3 TX: node TX -> pin 2, pin 3 -> node RX
Outputs: rain-gauge heater (low side), fan (high side) + tacho
load supply from common protected VIN rail through Q7
GPIO38 HIGH = heater on GPIO39 HIGH = fan on (both PWM capable)
J12: +V | HEAT- max 3 A J13: FAN+ | GND | TACH Fan max 0.5 A at 5 V (JP9 default), 1 A at VIN
Wind (Davis 6410)
J4 Davis RJ11: 2 yellow 3V3 (switched), 3 green DIR, 4 red GND, 5 black SPD R8 + JP2: pull-up for reed-switch vanes (jumper on); Q6: vane supply, VANE_EN LOW = on (GPIO34)
speed: tau 0.5-0.9 ms (min. contact time ~1.5 ms), direction: 10k / 1 uF
Rain (Davis 6466M)
J6 Davis RJ11: 3 reed switch, 4 GND (3/4 may be swapped) D20 TVS between jack and terminal U2 74LVC2G14: inverting
rain: tau ~10-15 ms
BME280 / I2C
J9: 3V3 | SDA | SCL | GND Cat5: SDA and SCL each twisted with a GND wire
Extra 4.7k pull-ups: JP1 SDA, JP11 SCL Separate 2-pin headers, rows 5.08 mm apart for cables longer than 0.5 m
1-Wire (DS18B20)
supply switched by GPIO47 (HIGH = on), 100 mA PTC up to 3 DS18B20

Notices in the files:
pcb/v4-full/universal-weather-node-v4-full.kicad_pcb:
UNIVERSAL WEATHER NODE V4 FULL REV 1.0 / franzenhof.com / CERN-OHL-P v2
